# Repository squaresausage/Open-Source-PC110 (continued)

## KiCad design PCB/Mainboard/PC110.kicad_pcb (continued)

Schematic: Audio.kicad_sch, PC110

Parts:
C6, C24, C50, C270: DNP; C_0402_1005Metric; not fitted
C9, C14, C23, C152, C160, C161, C162, C204, C209, C214: 10uF; C_1206_3216Metric
C10: DNP; C_1206_3216Metric; not fitted
C11, C13, C18, C21, C22, C25: 270nF; C_0603_1608Metric
C12: 250nF; C_0603_1608Metric
C15, C85, C208: 1nF; C_0402_1005Metric
C16, C154: 100pF; C_0402_1005Metric
C19, C151, C155, C157, C203, C205, C211, C212: 150nF; C_0402_1005Metric
C20: 1.5nF; C_0402_1005Metric
C44: 5.6nF; C_0402_1005Metric
C52, C53: 22pF; C_0402_1005Metric
C54: 2.7uF; C_0805_2012Metric
C57: 100nF; C_0603_1608Metric
C62: 120nF; C_0402_1005Metric
C68, C97, C149, C213, C215: 100nF; C_0402_1005Metric
C100, C150: 10nF; C_0603_1608Metric
C147, C153, C158, C248: 1uF; C_0603_1608Metric
C148, C159, C165: DNP; C_0402_1005Metric
C164: 330nF; C_0603_1608Metric
C166, C207: 300nF; C_0603_1608Metric
D3, D5: 3D
D12, D34: DNP; 3D; not fitted
D40: N; SOT-416L
J3: Audio-Jack
J7: SPKR
L2, L5, L7, L8, L13: 1.5uH; L_0603_1608Metric
Q6: ST3; SOT-416L
R23, R30, R67, R72, R75, R88, R195, R221, R370: 0; R_0402_1005Metric
R24: 4.7k; R_0402_1005Metric
R25, R29, R34: 1k; R_0402_1005Metric
R26, R32, R69, R73: 2.2k; R_0402_1005Metric
R27, R33, R77, R147, R217, R218, R224, R243, R244, R245, R247: 470k; R_0402_1005Metric
R28: 56; R_1206_3216Metric
R35, R37, R120, R121, R219, R223: 100k; R_0402_1005Metric
R36, R71, R74, R78, R220, R227, R258: 10k; R_0402_1005Metric
R47, R48, R50, R54, R55, R56, R64, R65: DNP; R_0402_1005Metric; not fitted
R70, R364: DNP; R_0402_1005Metric
R92: 47; R_0402_1005Metric
R222, R225: 6.8k; R_0402_1005Metric
R226: 120; R_1206_3216Metric
R250: 0; R_0805_2012Metric
R256: 100; R_0805_2012Metric
U4: ES488F; QFN-52
U5: 74HC14; TSSOP-14_4.4x5mm_P0.65mm
U10: YM3812; SOP-24
U11: NJM2904M; soic-8-small
U12: LM4861; SOIC-8-narrow
U17: 3E00; SOT-23-5
U18: VT74; TSSOP-14_4.4x5mm_P0.65mm
U20: 7W14; sso-8
U31: 3F01; SOT-23-5
U34: 74LV126; TSSOP-14_4.4x5mm_P0.65mm
U46: Y3014; SOP-16
U47: 3414A; SOIC-8
U48: DS1669; SOIC-8
U49: HD151015; SSOP-24_5.3x8.2mm_P0.65mm
U64: SN74LV126; TSSOP-14_4.4x5mm_P0.65mm
U66: SN74LV02; TSSOP-14_4.4x5mm_P0.65mm
U71: SN74LV32; TSSOP-14_4.4x5mm_P0.65mm
X2: 89G6821; XTAL-1

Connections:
/Audio/Enable_YMF_Bus: R147.1, U5.5, U10.3 (IC#), U31.1 (OUT), U34.1, U34.4, U34.10, U34.13
/Audio/PCMCIA_KB_sound: C25.2 (-), R35.1
/Audio/YMFDAC_OUTPUT: C11.2 (-), R26.1
Bowman_Audio_Vol_Dn: U48.7 (DnC); also elsewhere on the board
Bowman_Audio_Vol_Up: U48.2 (UpC); also elsewhere on the board
Chipset_Sound: R74.2; also elsewhere on the board
ESS_AEN: U4.40 (AEN); also elsewhere on the board
ESS_CLK: R70.1; also elsewhere on the board
ESS_DACK1#: U4.36 (DACK1#); also elsewhere on the board
ESS_DRDY: U4.21 (DRDY), U66.6
ESS_IRQ1: R29.1, U4.16 (IRQ1); also elsewhere on the board
ESS_IRQ2: U4.18 (IRQ2); also elsewhere on the board
ESS_Sound: C18.1 (+), U4.9 (LineOut)
IOR#: R364.1, U66.3, U66.5; also elsewhere on the board
KB_Sound: R78.1; also elsewhere on the board
MIC_J17: R30.2; also elsewhere on the board
MIC_in_pin: C6.2, J3.4 (MI), L13.2 (-)
Modem_Audio_Out: R32.1; also elsewhere on the board
unnamed: C10.1 (+), C23.1 (+), L7.1 (+)
unnamed: C10.2 (-), C23.2 (-), C154.2 (-), R227.2, U47.1
unnamed: C11.1 (+), C50.2, R72.1, U11.7
unnamed: C12.1 (+), U4.1 (FoutR)
unnamed: C12.2 (-), C24.2 (-), U4.2 (CinR)
unnamed: C13.1 (+), U48.6 (RW)
unnamed: C13.2 (-), R217.2, R218.2, U47.3 (+)
unnamed: C15.2 (-), R25.2, R26.2, R32.2, R34.2, R35.2, U47.6 (-)
unnamed: C18.2 (-), R34.1
unnamed: C20.2 (-), C21.2 (-), U4.8 (CinL)
unnamed: C21.1 (+), U4.7 (FoutL)
unnamed: C22.1 (+), U4.10 (ByPass)
unnamed: C25.1 (+), Q6.3 (C), R36.2
unnamed: C85.1 (+), R24.1, R121.1, U12.4 (IN-)
unnamed: C85.2 (-), J7.2, R121.2, U12.5 (OUT+)
unnamed: C147.1 (+), U48.1 (RH)
unnamed: C15.1 (+), C147.2 (-), R25.1, U47.7
unnamed: C150.1 (+), U4.4 (MIC)
unnamed: C150.2 (-), R221.1, R225.1
unnamed: C153.1, R37.2, R217.1
unnamed: C154.1 (+), R220.1, R227.1, U47.2 (-)
unnamed: C160.2 (-), C166.1 (+), R224.1, U4.11 (ByPass)
unnamed: C162.1 (+), R222.2, R225.2
unnamed: C164.2, R220.2
unnamed: C207.1 (+), R71.2
unnamed: C213.2, C214.2, R250.1
unnamed: C270.1, U64.11
unnamed: D3.2 (K), U5.6
unnamed: D5.2 (K), Q6.2 (B), R71.1, R74.1, R78.2
unnamed: J3.3 (G), L2.2 (-)
unnamed: C148.2, J3.5 (MO), L8.2 (-)
unnamed: C165.1, J3.2 (SI), L7.2 (-)
unnamed: C159.2, J3.1 (SO), L5.1 (+)
unnamed: J7.1, U12.8 (OUT-)
unnamed: C16.1, L5.2 (-), R24.2
unnamed: L8.1 (+), R30.1
unnamed: L13.1 (+), R221.2
unnamed: R67.1, R73.2, U11.1
unnamed: R370.2, U66.10
unnamed: C152.1, C155.2, C161.1, R226.1, U4.6 (CMR)
unnamed: U4.37 (IOR), U71.11
unnamed: U4.38 (IOW), U71.8
unnamed: R23.1, U4.52 (REF)
unnamed: U4.39 (RESET), U20.5
unnamed: C213.1, U4.44 (VCC_Bus), U49.24 (VCCB)
unnamed: C52.1, R70.2, U4.34 (Xin), X2.1
unnamed: C53.2, U4.35 (Xout), X2.2
unnamed: R77.1, U10.4 (AO), U34.11
unnamed: R244.2, U10.7 (CS#), U34.3
unnamed: R64.2, U4.23 (D0), U10.10 (D0), U49.22 (B0)
unnamed: R54.2, U4.24 (D1), U10.11 (D1), U49.21 (B1)
unnamed: R47.2, U4.25 (D2), U10.13 (D2), U49.20 (B2)
unnamed: R50.2, U4.28 (D3), U10.14 (D3), U49.19 (B3)
unnamed: R65.2, U4.29 (D4), U10.15 (D4), U49.18 (B4)
unnamed: R55.1, U4.30 (D5), U10.16 (D5), U49.17 (B5)
unnamed: R48.1, U4.31 (D6), U10.17 (D6), U49.16 (B6)
unnamed: R56.1, U4.32 (D7), U10.18 (D7), U49.15 (B7)
unnamed: R92.2, U10.24 (M)
unnamed: U10.21 (MO), U46.7 (SD)
unnamed: R243.2, U10.6 (RD#), U34.6
unnamed: U10.20 (SH), U46.4 (LOAD)
unnamed: U10.23 (SY), U46.10 (Clock)
unnamed: R245.2, U10.5 (WR#), U34.8
unnamed: C214.1, R75.1, U11.3 (+)
unnamed: R67.2, U11.2 (-), U46.16 (MP)
unnamed: R72.2, U11.6 (-)
unnamed: C157.1, C209.1, R256.1, U11.8 (V+), U46.1 (VDD)
unnamed: C157.2, C209.2, R250.2, U11.4 (V-), U46.12 (GND)
unnamed: C54.1, U12.2 (Bypass), U12.3 (IN+)
unnamed: C248.2, D40.3, R247.1, U12.1 (~SD)
unnamed: U18.2 (D), U18.6 (~Q), U18.11 (C)
unnamed: R92.1, U18.8 (~Q), U18.12 (D)
unnamed: C100.1, D34.3 (A), U31.5 (CD)
unnamed: C97.1, D34.1 (A), R195.2, U31.2 (VDD)
unnamed: R75.2, U46.14 (RB)
unnamed: C158.2, R27.1, R33.1, U47.5 (+)
unnamed: R219.2, U49.11 (A8)
unnamed: R223.1, U49.14 (B8)
unnamed: R364.2, R370.1, U49.2 (DIR)
unnamed: C270.2, D3.1 (A), D3.3 (A), R258.2, U49.23 (G#)
unnamed: U66.1, U66.8
unnamed: U66.4, U66.9
PCMCIA_Sound: C207.2 (-), R120.2; also elsewhere on the board
PNET1: C208.2, C211.2, C212.1, C215.1, R120.1, R258.1, U49.1 (VCCA), U64.13; also elsewhere on the board
PNET2: C68.1, C203.2, C204.2, C205.1, D34.2 (K), R28.2, R195.1, R243.1, R244.1, R245.1, R256.2, U10.1 (VCC), U12.6 (VDD), U18.1 (~R), U18.4 (~S), U18.10 (~S), U18.13 (~R), U18.14 (VCC); also elsewhere on the board
PNET6: C9.1, C14.1, C149.2, C151.1, R27.2, R28.1, R36.1, R37.1, R222.1, U47.8 (V+), U48.8 (V+)
PWRGD_shift: C248.1; also elsewhere on the board
PWRGD_shift_buff: U71.10, U71.13; also elsewhere on the board
SA1: U4.42 (A1); also elsewhere on the board
SA2: U4.43 (A2); also elsewhere on the board
SA3: U4.45 (A3); also elsewhere on the board
SA4: U4.46 (A4); also elsewhere on the board
SA5: U4.47 (A5); also elsewhere on the board
SA6: U4.48 (A6); also elsewhere on the board
SA7: U4.49 (A7); also elsewhere on the board
SA8: U4.50 (A8); also elsewhere on the board
SA9: U4.51 (A9); also elsewhere on the board
SD0: U49.3 (A0); also elsewhere on the board
SD1: U49.4 (A1); also elsewhere on the board
SD2: U49.5 (A2); also elsewhere on the board
SD3: U49.6 (A3); also elsewhere on the board
SD4: U49.7 (A4); also elsewhere on the board
SD5: U49.8 (A5); also elsewhere on the board
SD6: U49.9 (A6); also elsewhere on the board
SD7: U49.10 (A7); also elsewhere on the board
YMF_CLK: U18.3 (C); also elsewhere on the board
YMF_CS#_Buf: U4.14 (DIR), U34.2, U64.12, U66.2
YMF_RD#_Buf: U34.5, U71.12; also elsewhere on the board
YMF_SA0_A0: U4.41 (A0), U34.12; also elsewhere on the board
YMF_WR#_Buf: U34.9, U71.9; also elsewhere on the board

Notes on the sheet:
Device_Data_BUS
Device_Address_BUS

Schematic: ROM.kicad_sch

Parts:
C246: 150nF; C_0603_1608Metric
C249, C282: 150nF; C_0402_1005Metric
D19: N; SOT-416L
D20: 3D; SOT-416L
Q35: 8C; SOT-523
Q36: 7C; TSOT-23
R112: 47k; R_0402_1005Metric
R113, R327: 470k; R_0402_1005Metric
R320: 10k; R_0402_1005Metric
R321: 100k; R_0402_1005Metric
U24: E4; SOT-353
U36: MSM538032E; SOP48
U59: 28F002BX; Flash-40
U60: E3; SOT-353

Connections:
BIOS_SA17: U59.40 (A17); also elsewhere on the board
Bowman5_Buff: U60.1; also elsewhere on the board
Chipset_BIOS_CE#: U59.22 (CE#); also elsewhere on the board
Chipset_SA16: U59.1 (A16); also elsewhere on the board
D28_1: Q36.2 (E); also elsewhere on the board
MEMR#: U36.16 (OE#), U59.24 (OE#); also elsewhere on the board
MEMW#: U24.1; also elsewhere on the board
unnamed: C246.1 (+), D20.1, Q36.3 (C), R327.1, U59.11 (VPP)
unnamed: D19.1, D19.2, R112.2, U24.2
unnamed: Q35.1 (B), R321.2
unnamed: Q35.3 (C), R320.1
unnamed: Q36.1 (B), R320.2
unnamed: R321.1, U60.4
unnamed: D20.3, R113.2, U59.10 (RP#)
unnamed: U24.4, U59.9 (WE#)
OKI_CE#: U36.14 (CE#); also elsewhere on the board
OKI_SA12: U36.40 (A12); also elsewhere on the board
OKI_SA13: U36.39 (A13); also elsewhere on the board
OKI_SA14: U36.38 (A14); also elsewhere on the board
OKI_SA15: U36.37 (A15); also elsewhere on the board
OKI_SA16: U36.36 (A16); also elsewhere on the board
OKI_SA17: U36.5 (A17); also elsewhere on the board
OKI_SA18: U36.4 (A18); also elsewhere on the board
OKI_SA19: U36.45 (A19); also elsewhere on the board
PNET7: C249.2 (-), C282.1 (+), R112.1, U24.5 (VCC), U36.25 (VCC), U36.35 (BHE), U59.30 (VCC), U59.31 (VCC); also elsewhere on the board
PWRGD: D20.2; also elsewhere on the board
PWRGD_shift_buff: U60.2; also elsewhere on the board
Pluto_BIOS_WR_EN: D19.3; also elsewhere on the board
SA0: U59.21 (A0); also elsewhere on the board
SA1: U36.13 (A0), U59.20 (A1); also elsewhere on the board
SA2: U36.12 (A1), U59.19 (A2); also elsewhere on the board
SA3: U36.11 (A2), U59.18 (A3); also elsewhere on the board
SA4: U36.10 (A3), U59.17 (A4); also elsewhere on the board
SA5: U36.9 (A4), U59.16 (A5); also elsewhere on the board
SA6: U36.8 (A5), U59.15 (A6); also elsewhere on the board
SA7: U36.7 (A6), U59.14 (A7); also elsewhere on the board
SA8: U36.6 (A7), U59.8 (A8); also elsewhere on the board
SA9: U36.44 (A8), U59.7 (A9); also elsewhere on the board
SA10: U36.43 (A9), U59.36 (A10); also elsewhere on the board
SA11: U36.42 (A10), U59.6 (A11); also elsewhere on the board
SA12: U36.41 (A11), U59.5 (A12); also elsewhere on the board
SA13: U59.4 (A13); also elsewhere on the board
SA14: U59.3 (A14); also elsewhere on the board
SA15: U59.2 (A15); also elsewhere on the board
SD0: U36.17 (D0), U59.25 (DQ0); also elsewhere on the board
SD1: U36.19 (D1), U59.26 (DQ1); also elsewhere on the board
SD2: U36.21 (D2), U59.27 (DQ2); also elsewhere on the board
SD3: U36.23 (D3), U59.28 (DQ3); also elsewhere on the board
SD4: U36.26 (D4), U59.32 (DQ4); also elsewhere on the board
SD5: U36.28 (D5), U59.33 (DQ5); also elsewhere on the board
SD6: U36.30 (D6), U59.34 (DQ6); also elsewhere on the board
SD7: U36.32 (D7), U59.35 (DQ7); also elsewhere on the board
SD8: U36.18 (D8); also elsewhere on the board
SD9: U36.20 (D9); also elsewhere on the board
SD10: U36.22 (D10); also elsewhere on the board
SD11: U36.24 (D11); also elsewhere on the board
SD12: U36.27 (D12); also elsewhere on the board
SD13: U36.29 (D13); also elsewhere on the board
SD14: U36.31 (D14); also elsewhere on the board
SD15: U36.33 (D15); also elsewhere on the board

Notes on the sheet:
Device_Data_BUS
Device_Address_BUS
OKI_Extra_Address

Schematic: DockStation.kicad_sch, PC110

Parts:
C1: DNP; C_0402_1005Metric; not fitted
C2, C235, C237, C239, C265: 150nF; C_0402_1005Metric
C3, C7, C91, C93: 100nF; C_0402_1005Metric
C4: 1nF; C_0402_1005Metric
C86, C88: 180nF; C_0402_1005Metric
C89: 470nF; C_0603_1608Metric
C90, C92, C198, C243: 120nF; C_0402_1005Metric
C163, C167, C170, C199: 220pF; C_0402_1005Metric
C168, C238: 1uF; C_0603_1608Metric
C197, C240: 300nF; C_0603_1608Metric
C200, C201: 10uF; C_1206_3216Metric
C202: 150nF; C_0603_1608Metric
D1: 3D
D39, D55: s.3 5F; Diode
D52, D53, D54, D56, D57: K; SOT-416
D59: 3D; SOT-416L
EM5: R-array
F2: 1.0A; Fuse_1206_3216Metric
F3: 0.5A; Fuse_1206_3216Metric
J1: PS2
J8: Modem-Connector
J13: Docking Port
L1: 1.5uH; L_0603_1608Metric
L12: 300nH; L_0805_2012Metric
Q24: 6D; SOT-23
Q25, Q33, Q34: BH RT; SOT-89-3
Q32: 8B; SOT-416
R4: 4.7k; R_0402_1005Metric
R8: 300; R_0402_1005Metric
R122, R123, R124, R125, R127, R130, R135, R139, R144, R183, R187, R189, R190, R191, R194, R228, R302, R303, R305, R306, R307, R309, R311: 470k; R_0402_1005Metric
R181, R188, R192, R193, R289: 10k; R_0402_1005Metric
R230: 0; R_0805_2012Metric
R231: 0; R_0603_1608Metric
R238: 56; R_0603_1608Metric
R241: 8.2; R_1206_3216Metric_Pad1.30x1.75mm_HandSolder
R242: 7.5k; R_0402_1005Metric
R291, R297: 220; R_0402_1005Metric
R293: 22k; R_0402_1005Metric
R294: 1.2k; R_0402_1005Metric
RA2: 10k; R-array
U1: EA; SOT-353
U2: 7W32; sso-8
U3: HSDL-1000 X03; IRDA
U20: 7W14; sso-8
U26: 7W126; sso-8
U57: SN74LVT125; TSSOP-14_4.4x5mm_P0.65mm
U64: SN74LV126; TSSOP-14_4.4x5mm_P0.65mm
U71: SN74LV32; TSSOP-14_4.4x5mm_P0.65mm

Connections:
Dock_PWR_IN-: J13.53 (J13_53), J13.54 (J13_53), J13.55 (J13_53), J13.56 (J13_53), J13.57 (J13_53); also elsewhere on the board
EN_RS232: J13.79 (EN_RS232); also elsewhere on the board
Enable_IRDA_Buf: Q24.1 (B), R242.2, U26.1 (C), U26.7 (~PRE), U57.4, U57.10; also elsewhere on the board
FDC_ACK#: J13.71 (ACK#); also elsewhere on the board
FDC_AUTOFD#: J13.73 (AUTOFD#); also elsewhere on the board
FDC_BUSY: J13.22 (BUSY); also elsewhere on the board
FDC_CTS1#: J8.8 (CTS1#), R191.1; also elsewhere on the board
FDC_CTS2#: J13.82 (CTS2#), R303.2; also elsewhere on the board
FDC_DCD1#: J8.4 (DCD1#), R187.1; also elsewhere on the board
FDC_DCD2#: J13.17 (DCD2#), R309.2; also elsewhere on the board
FDC_DIR#: J13.7 (FDC_DIR#); also elsewhere on the board
FDC_DRATE0: R302.2, U57.2; also elsewhere on the board
FDC_DRATE1: R306.2, U57.12; also elsewhere on the board
FDC_DSKCHG#: J13.12 (FDC_DSKCHG#), R122.2; also elsewhere on the board
FDC_DSR1: J8.7 (DSR1), R189.1; also elsewhere on the board
FDC_DSR2#: J13.84 (DSR2#), R305.2; also elsewhere on the board
FDC_DTR1#: R192.1, U64.9; also elsewhere on the board
FDC_DTR2#: J13.20 (DTR2#); also elsewhere on the board
FDC_ERROR#: J13.77 (ERROR#); also elsewhere on the board
FDC_HDSEL#: J13.11 (FDC_HDSEL#); also elsewhere on the board
FDC_INIT#: J13.72 (INIT#); also elsewhere on the board
FDC_IRRX_RXD2: U26.3 (~Q), U57.8; also elsewhere on the board
FDC_IRTX_TXD2: R183.2, U26.2 (D), U57.5; also elsewhere on the board
FDC_PD0: J13.30 (PD0); also elsewhere on the board
FDC_PD1: J13.29 (PD1); also elsewhere on the board
FDC_PD2: J13.28 (PD2); also elsewhere on the board
FDC_PD3: J13.27 (PD3); also elsewhere on the board
FDC_PD4: J13.26 (PD4); also elsewhere on the board
FDC_PD5: J13.25 (PD5); also elsewhere on the board
FDC_PD6: J13.76 (PD6); also elsewhere on the board
FDC_PD7: J13.24 (PD7); also elsewhere on the board
FDC_PE: J13.78 (PE); also elsewhere on the board
FDC_RDATA#: J13.91 (FDC_RDATA#), R307.2; also elsewhere on the board
FDC_RI1#: J8.5 (RI1#), R190.1; also elsewhere on the board
FDC_RI2#: J13.81 (RI2#), R311.1; also elsewhere on the board
FDC_RTS1#: R193.1, U64.5; also elsewhere on the board
FDC_RTS2#: J13.83 (RTS2#); also elsewhere on the board
FDC_RXD1: J8.10 (RXD1), R194.1; also elsewhere on the board
FDC_SLCT: J13.23 (SLCT); also elsewhere on the board
FDC_SLCTIN#: J13.74 (SLCTIN#); also elsewhere on the board
FDC_STEP#: J13.94 (FDC_STEP#); also elsewhere on the board
FDC_STROBE#: J13.31 (STROBE#); also elsewhere on the board
FDC_TRK0#: J13.9 (FDC_TRK0), R124.2; also elsewhere on the board
FDC_TXD1: R188.1, U64.2; also elsewhere on the board
FDC_TXD2_EN: R8.1, U2.5, U57.6
FDC_UART1_EN: U64.1, U64.4, U64.10; also elsewhere on the board
FDC_WDATA#: J13.8 (FDC_WDATA#); also elsewhere on the board
FDC_WGATE#: J13.93 (FDC_WGATE#); also elsewhere on the board
FDC_WRTPRT#: J13.10 (FDC_WRTPRT#), R125.1; also elsewhere on the board
FDD_Bowman: J13.90 (FDD_Bowman), R144.2; also elsewhere on the board
FDD_DRSEL: J13.5 (FDD_DRSEL); also elsewhere on the board
FDD_INDEX#: J13.4 (FDD_INDEX#), R123.2; also elsewhere on the board
FDD_MOTEN: J13.6 (FDD_MOTEN); also elsewhere on the board
FDD_Pluto1: J13.98 (FDD_Pluto1); also elsewhere on the board
FDD_Pluto2: J13.97 (FDD_Pluto2); also elsewhere on the board
FDD_Pluto3: J13.95 (FDD_Pluto3); also elsewhere on the board
FDD_Pluto4: J13.92 (FDD_Pluto4); also elsewhere on the board
KB_INIT1: EM5.5, J13.14 (KB_INT1), RA2.5 (R4.2); also elsewhere on the board
KB_INIT2: EM5.6, J13.15 (KB_INT2), RA2.6 (R3.2); also elsewhere on the board
KB_INIT3: EM5.8, J13.86 (KB_INT3), RA2.8 (R1.2); also elsewhere on the board
KB_INIT4: EM5.7, J13.87 (KB_INT4), RA2.7 (R2.2); also elsewhere on the board
KB_SPKUP_DN: D59.3 (A), J13.63 (KB_SPKUP_DN); also elsewhere on the board
KB_SRDY#_shift: R294.1; also elsewhere on the board
M38_P16_R86: J13.62 (M38_P16); also elsewhere on the board
M38_P34: J13.38 (M38_P34); also elsewhere on the board
M38_P46: J13.39 (M38_P46); also elsewhere on the board
M38_P67: J13.61 (M38_P67); also elsewhere on the board
MN192_VSEN#: J8.16 (VSEN#); also elsewhere on the board
MN195_U1RD#: J8.3 (U1RD#); also elsewhere on the board
Modem_Audio_Out: C89.1 (+); also elsewhere on the board
Modem_VSDA#: J8.17 (VSDA#), R127.1; also elsewhere on the board
unnamed: C1.2 (-), U2.1, U3.1 (IRDA_RXA)
unnamed: C4.1 (+), D1.1 (A), D1.3 (A), R4.1, U1.2
unnamed: C7.1 (+), J1.7 (PS2_Pluto), L1.2
unnamed: C89.2 (-), J8.18 (VPCK#)
unnamed: C92.2 (-), F3.1, J13.16 (PS/2_Power), L12.1, RA2.1 (R1.1), RA2.2 (R2.1), RA2.3 (R3.1), RA2.4 (R4.1)
unnamed: C163.2 (-), EM5.3, J1.6 (KB_INIT2)
unnamed: C167.2 (-), EM5.4, J1.2 (KB_INIT1)
unnamed: C168.2 (-), U3.3 (PIN_Bypass)
unnamed: C170.1 (+), EM5.1, J1.5 (KB_INIT3)
unnamed: C197.2 (-), U3.5 (Daylight_Cancellation)
unnamed: C198.1 (+), J1.4 (5V), L12.2
unnamed: C199.1 (+), EM5.2, J1.3 (KB_INIT4)
unnamed: C200.2 (-), R241.1, U3.8 (IRDA_LED_A)
unnamed: C201.1 (+), C202.2 (-), R238.1, U3.6 (IRDA_Supply)
unnamed: C238.1 (+), Q33.1 (B), R293.1, R297.2
unnamed: C93.1 (+), C238.2 (-), C239.2 (-), J13.13 (FDD_PWR), J13.88 (FDD_PWR), J13.89 (FDD_PWR), Q33.2 (C)
unnamed: C240.1 (+), Q34.1 (B), R294.2
unnamed: C240.2 (-), F3.2, Q34.2 (C)
unnamed: D1.2 (K), R4.2, U2.3
unnamed: D39.2 (A), D55.2 (A), J13.46 (PNET4), J13.48 (PNET4)
unnamed: J1.1 (GND), R231.2
unnamed: J1.8 (GND), R230.2
unnamed: J8.6 (DRT1#), U64.8
unnamed: J8.9 (RTS1#), U64.6
unnamed: J8.11 (TXD1), U64.3
unnamed: J13.96 (FDD_DRATE0), U57.3
unnamed: J13.3 (FDD_DRATE1), U57.11
unnamed: J8.21 (ADCK#), J13.59 (Modem_ADCK#)
unnamed: J8.20 (IRQ1#), J13.60 (Modem_IRQ1#)
unnamed: J8.24 (RSRVD2), J13.42 (Modem_RSRVD1)
unnamed: J8.23 (RSRVD1), J13.41 (Modem_RSRVD2)
unnamed: J8.22 (S11), J13.58 (Modem_S11)
unnamed: J8.19 (VPDA#), J13.52 (Modem_VPDA#)
unnamed: J13.18 (RXD2), R135.1, U26.5 (Q)
unnamed: J13.19 (TXD2), U26.6 (~CLR)
unnamed: Q24.3 (C), R238.2
unnamed: Q25.1 (B), R242.1
unnamed: Q25.2 (C), R241.2
unnamed: Q32.1 (B), R289.2
unnamed: Q32.3 (C), R291.1
unnamed: F2.1, Q33.3 (E), R293.2
unnamed: R289.1, U20.2
unnamed: R291.2, R297.1
unnamed: U1.4, U2.2
unnamed: U2.7, U57.9
unnamed: R8.2, U3.7 (IRDA_TXD)
unnamed: U20.6, U57.1, U57.13, U71.3
PNET1: D52.2 (K), D53.2 (K), D54.2 (K), D56.2 (K), D57.2 (K), R127.2, R228.1, U64.14 (VCC); also elsewhere on the board
PNET2: C2.1 (+), C3.1 (+), C235.1 (+), C237.1 (+), J13.21 (PNET2), J13.80 (PNET2), R183.1, U1.5 (VCC), U2.8 (VCC); also elsewhere on the board
PNET4: D39.1 (K), D55.1 (K); also elsewhere on the board
PNET7: R130.1, R139.1, R144.1; also elsewhere on the board
PS2_L1_Pluto: L1.1, R228.2; also elsewhere on the board
PWRGD_shift_buff: R181.2, U71.1; also elsewhere on the board
Pluto_Dock_IO1: J13.2 (Pluto_Dock1), R139.2; also elsewhere on the board
Pluto_Dock_IO2: J13.99 (Pluto_Dock2), R130.2; also elsewhere on the board
Pluto_IRDA_OUT: U2.6; also elsewhere on the board
Pluto_Switched_PNET5: C86.1 (+), J8.12 (PNET5_Pluto), J8.15 (PNET5_Pluto), R187.2, R189.2, R190.2, R191.2, R194.2; also elsewhere on the board
U71_OR1_IN2: U71.2; also elsewhere on the board
VCC: C88.2 (-), J8.2 (VCC), J8.25 (VCC); also elsewhere on the board
VGA_Blue: D54.3 (COM), J13.65 (VGA_Blue); also elsewhere on the board
VGA_Green: D53.3 (COM), J13.67 (VGA_Green); also elsewhere on the board
VGA_HSync: D56.3 (COM), J13.36 (VGA_HSync); also elsewhere on the board
VGA_Red: D52.3 (COM), J13.69 (VGA_Red); also elsewhere on the board
VGA_VSync: D57.3 (COM), J13.33 (VGA_VSync); also elsewhere on the board
YellowWire1_2: R181.1; also elsewhere on the board

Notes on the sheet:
Enables all external PS/2 devices; PS/2 conn on PC110 and dock

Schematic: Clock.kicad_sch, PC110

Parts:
C56: 100nF; C_0402_1005Metric
C59: 10nF; C_0603_1608Metric
C227, C256: 150nF; C_0402_1005Metric; Rating V
C230, C257, C261: DNP; C_0402_1005Metric; Rating V
C232: 10uF; C_1206_3216Metric; Rating V
C242: 100nF; C_0402_1005Metric; Rating V
C254, C260: 1nF; C_0402_1005Metric; Rating V
C258: 220pF; C_0402_1005Metric; Rating V
C259: 330nF; C_0603_1608Metric; Rating V
D9: DNP; 3D
Q31: MUN2114; SOT-23
R79: 0; R_0402_1005Metric
R91: 470k; R_0402_1005Metric
R275: 4.7k; R_0402_1005Metric
R284: 10; R_0805_2012Metric
R332, R340, R341, R348, R350, R359: 33; R_0402_1005Metric
R344: DNP; R_0402_1005Metric
R353: 56; R_0402_1005Metric
R357, R358: 47; R_0402_1005Metric
U16: BD53E31; SOT-23-5
U62: 74LS125; TSSOP-14_4.4x5mm_P0.65mm
U63: AV9154A-27; SOIC-16W
U66: 74LS02; TSSOP-14_4.4x5mm_P0.65mm
X4: 59G3482; XTAL-6

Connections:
Bowman_CLK: R340.2; also elsewhere on the board
Chipset_2XCPU_CLK: R359.2; also elsewhere on the board
Chipset_CLK: R341.1; also elsewhere on the board
ESS_CLK: R344.2; also elsewhere on the board
FDC_CLK: R332.2; also elsewhere on the board
unnamed: C227.2 (-), D9.2 (K), Q31.3 (C), R79.1, R275.1, R284.1, U63.10 (FS2), U63.16 (FS0)
unnamed: C230.2 (-), C257.2 (-), U63.2 (X2), X4.2
unnamed: C232.2 (-), C258.2 (-), C259.2 (-), C260.2 (-), R284.2, U63.4 (VCC), U63.13 (VCC)
unnamed: C257.1 (+), C261.1 (+), U63.3 (X1), X4.1
unnamed: Q31.1 (B), U66.13
unnamed: R332.1, R340.1, U62.8
unnamed: R341.2, R348.2, U62.6
unnamed: R344.1, R353.1, U62.11
unnamed: R350.2, U62.3
unnamed: R357.1, U62.2, U62.5, U62.12
unnamed: R358.1, U62.9
unnamed: C59.1, D9.3 (A), U16.5 (CD)
unnamed: R91.1, U16.1 (OUT), U63.9 (OE)
unnamed: C56.1, D9.1 (A), R79.2, U16.2 (VDD)
unnamed: R359.1, U63.14 (3XCPUCLK)
unnamed: R357.2, U63.11 (14.318MHz)
unnamed: R358.2, U63.6 (24MHz)
PNET1: C242.2 (-), C254.2 (-), C256.2 (-), Q31.2 (E), U62.14 (VCC), U66.14 (VCC); also elsewhere on the board
PWRGD: U66.12; also elsewhere on the board
Pluto_CLK: R348.1; also elsewhere on the board
RESET: U66.11; also elsewhere on the board
VGA_CLK: R350.1; also elsewhere on the board
YMF_CLK: R353.2; also elsewhere on the board

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
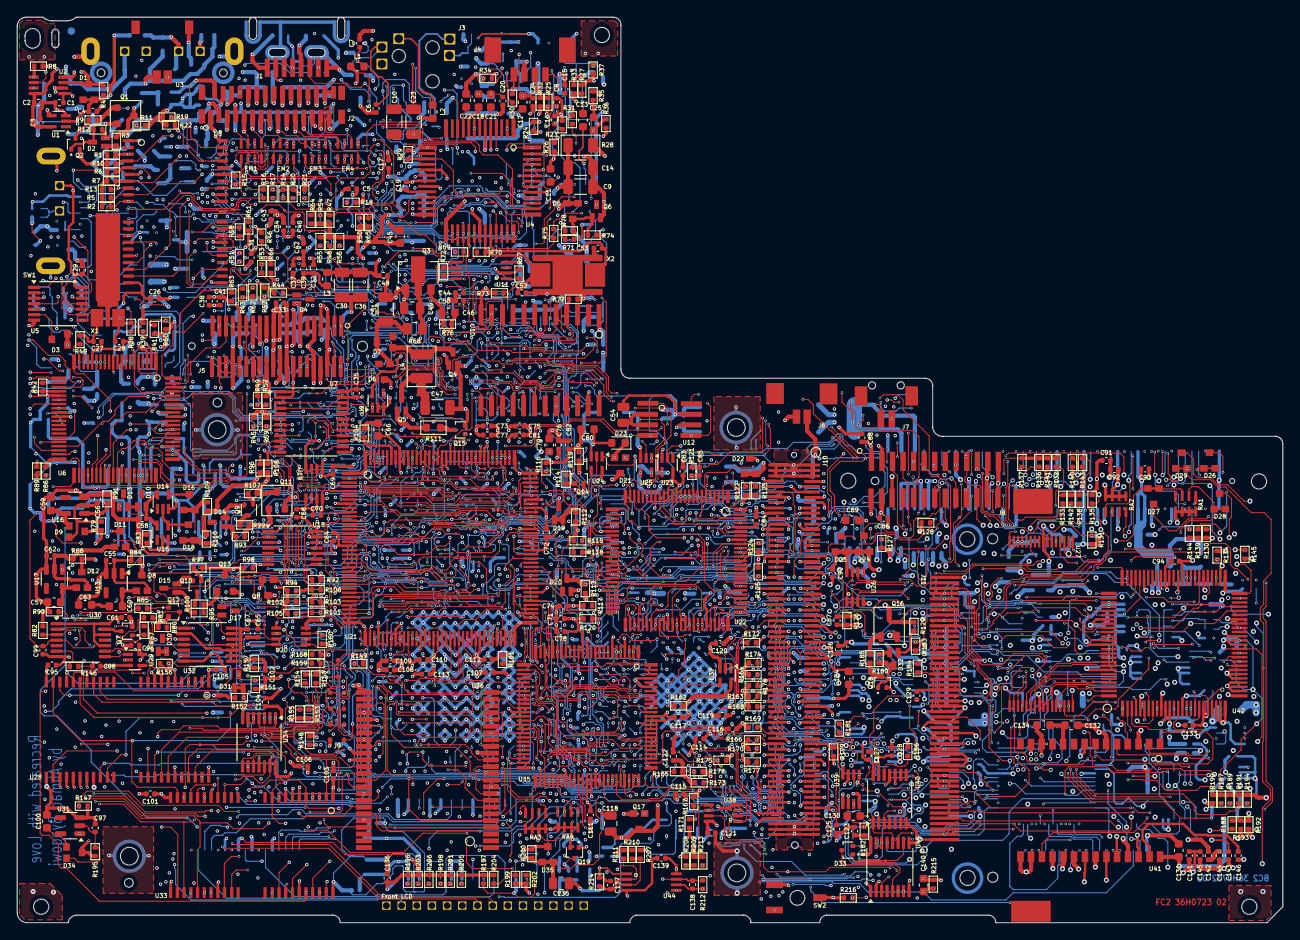
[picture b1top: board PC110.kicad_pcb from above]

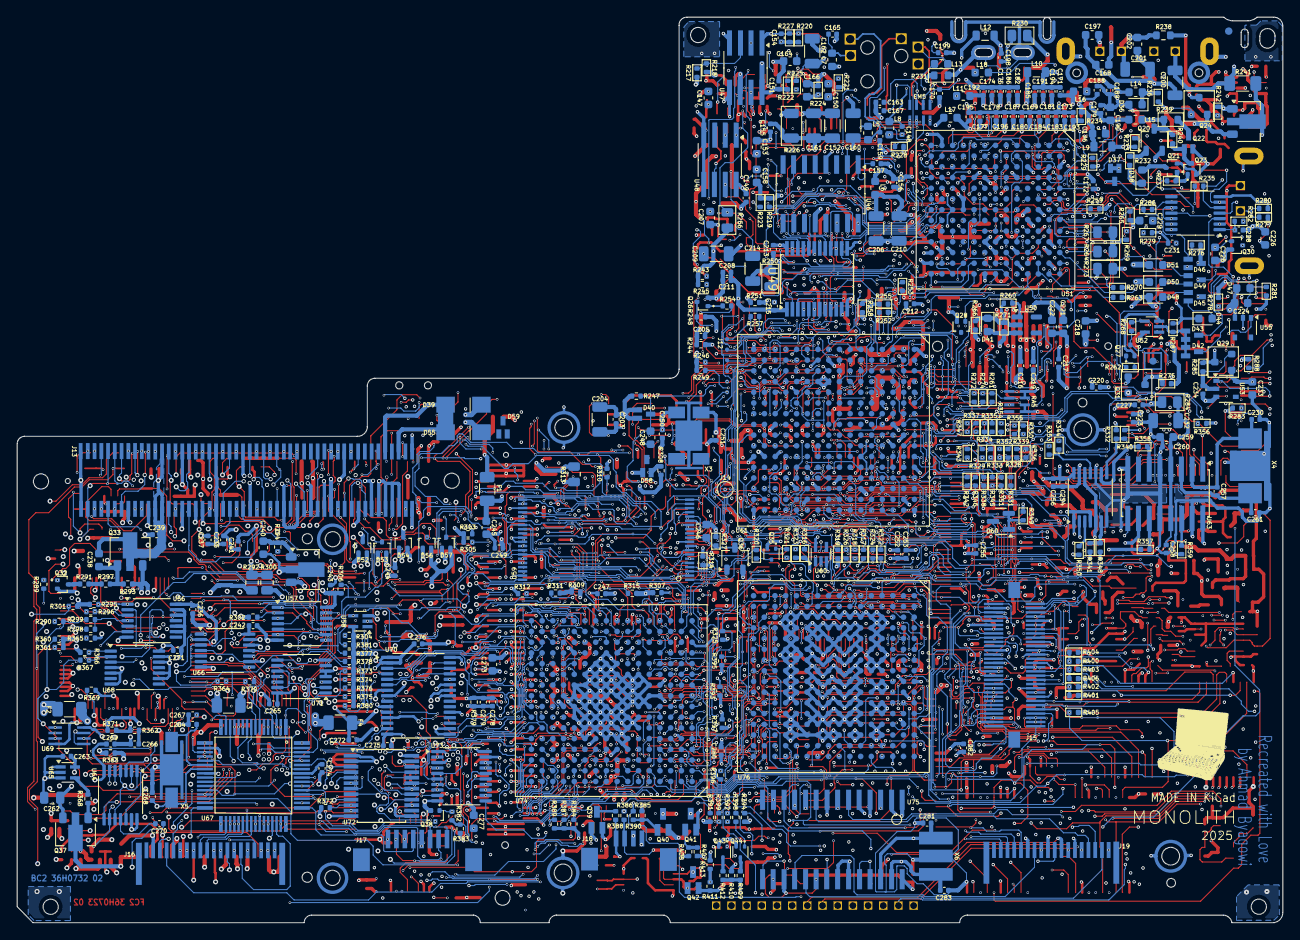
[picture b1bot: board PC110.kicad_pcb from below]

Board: 10 copper layers, 150.1 x 107.4 mm, 936 parts (448 on the bottom side), 1141 nets.

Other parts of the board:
G1: LOGO; logo

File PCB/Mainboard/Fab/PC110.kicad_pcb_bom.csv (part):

Designator,Quantity,Value,Footprint,Package,MPN,DNP,Mount_Type,Description
C1,1,DNP,C_0402_1005Metric,,,Yes,smt,
C10,1,DNP,C_1206_3216Metric,,,Yes,smt,
"C100, C131, C150, C190, C222, C224, C245, C46, C59",9,10nF,C_0603_1608Metric,,,,smt,
"C101, C109, C61, C74, C86, C88",6,180nF,C_0402_1005Metric,,,,smt,
"C102, C113, C198, C243, C244, C255, C279, C29, C41, C62, C73, C87, C90, C92",14,120nF,C_0402_1005Metric,,,,smt,
"C103, C104, C105, C108, C112, C123, C126, C128, C136, C142, C143, C151, C155, C157, C17, C19, C2, C203, C205, C211, C212, C216, C217, C219, C220, C223, C227, C231, C234, C235, C237, C239, C249, C253, C256, C26, C265, C271, C272, C278, C282, C31, C32, C33, C35, C39, C42, C5, C65, C8, C95, C96",52,150nF,C_0402_1005Metric,,,,smt,
"C106, C107, C110, C111, C125, C137, C138, C15, C179, C188, C208, C247, C252, C254, C260, C34, C37, C38, C4, C40, C43, C64, C69, C71, C77, C78, C81, C85",28,1nF,C_0402_1005Metric,,,,smt,
"C11, C13, C18, C21, C22, C25, C45",7,270nF,C_0603_1608Metric,,,,smt,
"C114, C115, C116, C117, C119, C120, C121, C122, C127, C129, C133, C139, C141, C146, C149, C156, C172, C189, C213, C215, C236, C241, C242, C263, C274, C275, C276, C280, C3, C55, C56, C58, C67, C68, C7, C70, C72, C75, C76, C82, C83, C84, C91, C93, C94, C97",46,100nF,C_0402_1005Metric,,,,smt,
"C118, C135, C54",3,2.7uF,C_0805_2012Metric,,,,smt,
C12,1,250nF,C_0603_1608Metric,,,,smt,
"C124, C134, C202, C218, C221, C246, C273",7,150nF,C_0603_1608Metric,,,,smt,
"C130, C140, C147, C153, C158, C168, C225, C226, C229, C238, C248, C277, C66, C79",14,1uF,C_0603_1608Metric,,,,smt,
"C132, C57, C60, C63",4,100nF,C_0603_1608Metric,,,,smt,
"C14, C152, C160, C161, C162, C200, C201, C204, C206, C209, C210, C214, C23, C232, C30, C36, C51, C9",18,10uF,C_1206_3216Metric,,,,smt,
"C144, C145, C154, C16, C228, C99",6,100pF,C_0402_1005Metric,,,,smt,
C148,1,DNP,C_0402_1005Metric,,,Yes,smt,
C159,1,DNP,C_0402_1005Metric,,,Yes,smt,
"C163, C167, C170, C199, C258, C269",6,220pF,C_0402_1005Metric,,,,smt,
"C164, C233, C259",3,330nF,C_0603_1608Metric,,,,smt,
C165,1,DNP,C_0402_1005Metric,,,Yes,smt,
"C166, C197, C207, C240",4,300nF,C_0603_1608Metric,,,,smt,
"C169, C171, C173, C174, C175, C177, C178, C180, C181, C182, C183, C184, C185, C186, C187, C191, C192, C193, C194, C195, C196, C264",22,56pF,C_0402_1005Metric,,,,smt,
"C176, C89",2,470nF,C_0603_1608Metric,,,,smt,
C20,1,1.5nF,C_0402_1005Metric,,,,smt,
C230,1,DNP,C_0402_1005Metric,,,Yes,smt,
C24,1,DNP,C_0402_1005Metric,,,Yes,smt,
"C250, C251, C27, C28",4,18pF,C_0402_1005Metric,,,,smt,
C257,1,DNP,C_0402_1005Metric,,,Yes,smt,
C261,1,DNP,C_0402_1005Metric,,,Yes,smt,
C262,1,1.5uF,C_0805_2012Metric,,,,smt,
C266,1,180pF,C_0402_1005Metric,,,,smt,
C267,1,DNP,C_0402_1005Metric,,,Yes,smt,
C268,1,56pf,C_0402_1005Metric,,,,smt,
C270,1,DNP,C_0402_1005Metric,,,Yes,smt,
"C281, C283",2,39pF,C_0402_1005Metric,,,,smt,
C44,1,5.6nF,C_0402_1005Metric,,,,smt,
C47,1,5.6uF,C_1206_3216Metric,,,,smt,
C48,1,330nF,C_0402_1005Metric,,,,smt,
C49,1,2.2uF,C_0805_2012Metric,,,,smt,
C50,1,DNP,C_0402_1005Metric,,,Yes,smt,
"C52, C53",2,22pF,C_0402_1005Metric,,,,smt,
C6,1,DNP,C_0402_1005Metric,,,Yes,smt,
C80,1,1uF,C_0603_1608Metric,,,Yes,smt,
C98,1,330pF,C_0402_1005Metric,,,,smt,
"D1, D16, D18, D21, D22, D24, D25, D26, D27, D28, D29, D3, D35, D5",14,3D,3D,,,,smt,
"D10, D13, D2, D32, D58",5,K,SOT-416L,,,,smt,
D11,1,DNP,3D,,,Yes,smt,
D12,1,DNP,3D,,,Yes,smt,
"D14, D15, D17, D19, D30, D31, D37, D4, D40, D42, D43, D45, D46, D49",14,N,SOT-416L,,,,smt,
"D20, D59",2,3D,SOT-416L,,,,smt,
D23,1,92,D_0603_1608Metric,,,,smt,
D33,1,N,SOT-416,,,,smt,
D34,1,DNP,3D,,,Yes,smt,
D36,1,71,D_0603_1608Metric,,,,smt,
D38,1,40,D_0603_1608Metric,,,,smt,
"D39, D55",2,s.3 5F,Diode,,,,smt,
"D41, D47",2,24,D_0603_1608Metric,,,,smt,
D44,1,83,D_0603_1608Metric,,,,smt,
D48,1,A2,D_0603_1608Metric,,,,smt,
D50,1,26,D_0603_1608Metric,,,,smt,
D51,1,C6,D_0603_1608Metric,,,,smt,
"D52, D53, D54, D56, D57",5,K,SOT-416,,,,smt,
"D6, D7",2,Q,3D,,,,smt,
D60,1,3D,SOT-23,,,,smt,
D8,1,DNP,3D,,,Yes,smt,
D9,1,DNP,3D,,,Yes,smt,
"EM1, EM2, EM3, EM4, EM5",5,R-array,R-array,,,,smt,
"F1, F3, F4",3,0.5A,Fuse_1206_3216Metric,,,,smt,
F2,1,1.0A,Fuse_1206_3216Metric,,,,smt,
J1,1,PS2,PS2,,,,smt,
J10,1,PCMCIA,PCMCIA,,,,smt,
J11,1,CF-card,CF-card,,,,smt,
J12,1,Debug-6,Debug-6,,,,smt,
J13,1,Docking Port,Docking Port,,,,smt,
J15,1,RAM Module,RAM Module,,,,smt,
J16,1,Flat-20,Flat-20,,,,smt,
J17,1,Flat-8,Flat-8,,,,smt,
J18,1,Flat-4,Flat-4,,,,smt,
J19,1,Flat-18,Flat-18,,,,smt,
J2,1,LCD_connector,LCD_connector,,,,smt,
J3,1,Audio-Jack,Audio-Jack,,,,smt,
J4,1,connector-4,connector-4,,,,smt,
J5,1,PSU_Connector,PSU_Connector,,,,smt,
J6,1,BridgeBatt,BridgeBatt,,,,smt,
J7,1,SPKR,SPKR,,,,smt,
J8,1,Modem-Connector,Modem-Connector,,,,smt,
J9,1,Debug-10,Debug-10,,,,smt,
"L1, L11, L13, L14, L15, L16, L17, L18, L2, L3, L5, L6, L7, L8",14,1.5uH,L_0603_1608Metric,,,,smt,
"L10, L12, L9",3,300nH,L_0805_2012Metric,,,,smt,
L4,1,68uH,L_1210_3225Metric,,,,smt,
"Q1, Q11, Q13",3,IS6,SOT-23,,,,smt,
"Q10, Q12, Q14, Q18, Q2, Q26, Q27, Q30, Q38, Q7",10,8C,SOT-416,,,,smt,
"Q15, Q19, Q21, Q23, Q32",5,8B,SOT-416,,,,smt,
Q16,1,IS6,TSOT-23,,,,smt,
"Q17, Q8",2,6D,3D,,,,smt,
"Q20, Q36",2,7C,TSOT-23,,,,smt,
"Q22, Q4",2,YQ,SOT-416L,,,,smt,
"Q24, Q31",2,6D,SOT-23,,,,smt,
"Q25, Q33, Q34, Q37",4,BH RT,SOT-89-3,,,,smt,
Q28,1,8LR,SOT-416,,,,smt,
Q29,1,DNP,SOT-23,,,Yes,smt,
Q3,1,582 B74,SOT-89-3,,,,smt,
"Q35, Q9",2,8C,SOT-523,,,,smt,
"Q39, Q40",2,HQ,TSOT-23,,,,smt,
"Q41, Q42",2,CQ,TSOT-23,,,,smt,
"Q43, Q44",2,8B,SOT-523,,,,smt,
Q5,1,HQ,SOT-416L,,,,smt,
Q6,1,ST3,SOT-416L,,,,smt,
"R1, R10, R102, R105, R11, R113, R119, R122, R123, R124, R125, R126, R127, R128, R13, R130, R135, R139, R144, R146, R147, R148, R15, R152, R156, R158, R160, R161, R162, R173, R18, R182, R183, R186, R187, R189, R19, R190, R191, R194, R2, R215, R216, R217, R218, R22, R224, R228, R229, R233, R235, R243, R244, R245, R247, R248, R259, R262, R269, R27, R278, R282, R287, R302, R303, R305, R306, R307, R309, R311, R314, R315, R327, R33, R360, R361, R379, R5, R6, R61, R7, R77, R80, R82, R83, R90, R91, R94",88,470k,R_0402_1005Metric,,,,smt,
"R100, R291, R297",3,220,R_0402_1005Metric,,,,smt,
"R101, R103, R106, R149, R154, R159, R251, R252, R255, R257, R261, R272, R274, R317, R318, R322, R324, R326, R329, R332, R333, R334, R335, R337, R338, R340, R341, R342, R343, R345, R346, R347, R348, R350, R352, R357, R359, R46, R53",39,33,R_0402_1005Metric,,,,smt,
"R104, R112, R114, R117, R165, R171, R177, R196, R197, R200, R204, R206, R240, R246, R249, R254, R280, R288, R312, R356, R385, R39, R393, R397, R40, R408, R411, R85, R93, R95, R96",31,47k,R_0402_1005Metric,,,,smt,
"R107, R276, R383",3,33k,R_0402_1005Metric,,,,smt,
"R108, R185, R24, R263, R265, R270, R275, R279, R283, R304, R328, R330, R331, R336, R339, R351, R354, R355, R373, R374, R375, R376, R377, R378, R38, R380, R381, R4, R42, R86, R89, R9, R98",33,4.7k,R_0402_1005Metric,,,,smt,
"R109, R110, R115, R134, R143, R163, R164, R166, R168, R169, R170, R172, R174, R175, R176, R178, R179, R181, R188, R192, R193, R198, R203, R220, R227, R232, R237, R258, R281, R289, R320, R325, R36, R365, R384, R389, R391, R395, R396, R41, R71, R74, R78, R97",44,10k,R_0402_1005Metric,,,,smt,
R111,1,100,R_0603_1608Metric,,,,smt,
"R116, R118, R120, R121, R150, R151, R153, R155, R157, R167, R201, R205, R209, R212, R214, R219, R223, R234, R268, R310, R321, R349, R35, R363, R37, R372, R390, R401, R404, R405, R406, R407, R413, R44, R45, R49, R57, R59, R81, R87",40,100k,R_0402_1005Metric,,,,smt,
R12,1,182k,R_0402_1005Metric,,,,smt,
"R129, R260",2,133k,R_0402_1005Metric,,,,smt,
R131,1,DNP,R_0402_1005Metric,,,Yes,smt,
"R132, R133, R137, R362, R371",5,2k,R_0402_1005Metric,,,,smt,
"R136, R138, R140, R141, R142, R25, R29, R316, R319, R323, R34, R386, R76",13,1k,R_0402_1005Metric,,,,smt,
"R14, R17, R20, R308",4,10,R_0402_1005Metric,,,,smt,
R145,1,DNP,R_0402_1005Metric,,,Yes,smt,
"R16, R195, R21, R221, R23, R285, R295, R299, R30, R366, R367, R370, R51, R58, R67, R72, R75, R79, R84, R88",20,0,R_0402_1005Metric,,,,smt,
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
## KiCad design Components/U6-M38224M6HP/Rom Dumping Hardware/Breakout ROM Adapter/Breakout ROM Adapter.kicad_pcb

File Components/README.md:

## PROM Dump

Here is a list of microcontrollers used on the PC110.
You can find the binary used on them with the disassembler approach.

|Designator|Part#  |Functions           |Notes                             |
|----------|-------|--------------------|----------------------------------|
|U6        |M38223*|Power Control, Front LCD & More|[Notes](U6-M38224M6HP/)|
|U67       |M38813*|Keyboard Controller|[Notes](U67-M38813E4HP/)           |

## Die level investigation

This part is a collaboration with [John McMaster](https://siliconpr0n.org/archive/doku.php?id=ibm:pc110)

|Designator|Part#      |Functions           |Images | Notes                             |
|----------|-----------|--------------------|-------|-----------------------------------|
|U75       |D17137AGT  |Trackpoint          |[Images](https://siliconpr0n.org/archive/doku.php?id=mcmaster:nec:d17137agt)|[Notes](U75-D17137AGT/)|
|U35       |Pluto      |Gate Array          |[Images](https://siliconpr0n.org/archive/doku.php?id=mcmaster:rios:z10s10922-00)|[Notes](U35-Pluto/)|
|U21       |Bowman     |Gate Array          |[Images](https://siliconpr0n.org/archive/doku.php?id=mcmaster:rios:63g33f1017)|[Notes](U21-Bowman/)|
|U61       |VL82C420FC5|Chipset, RTC, DMA, Intrupt Controller, Timer             |[Images](https://siliconpr0n.org/archive/doku.php?id=mcmaster:rios:vl82c420fc5-c)|[Notes](U61-VL82C420FC5/)|

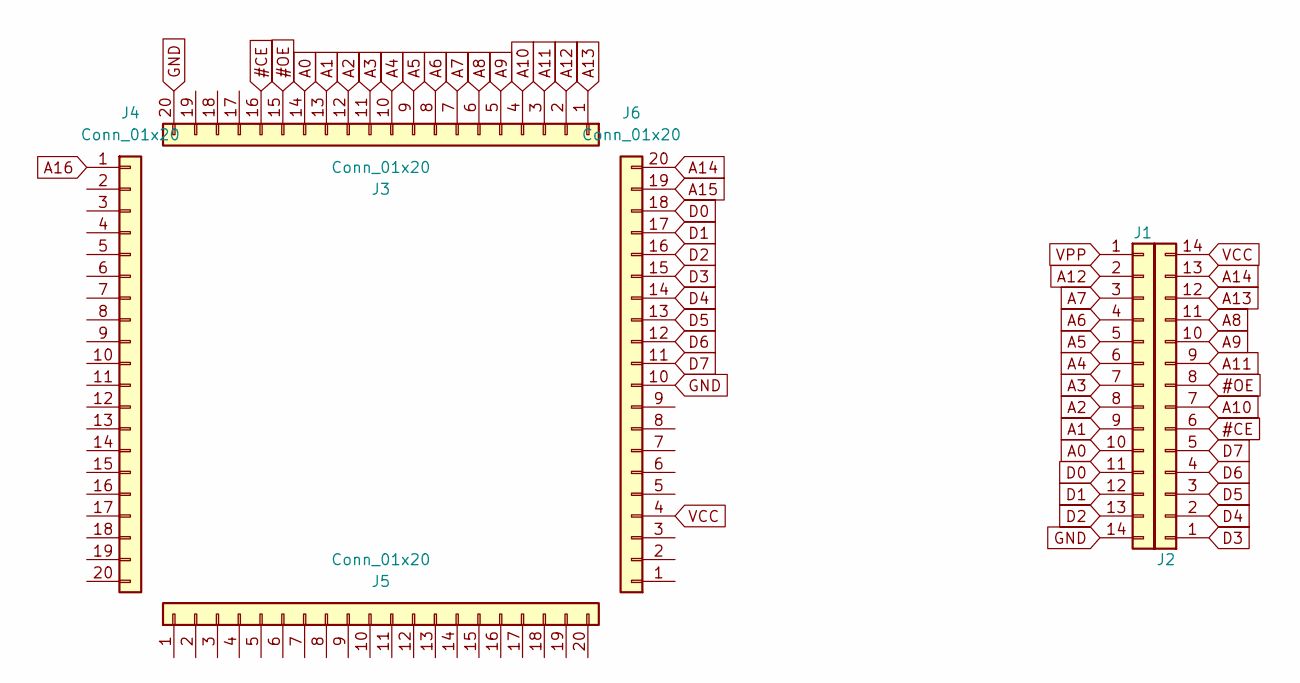
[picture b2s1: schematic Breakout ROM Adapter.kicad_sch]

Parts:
J1, J2: Conn_01x14; PinHeader_1x14_P2.54mm_Vertical
J3, J4, J5, J6: Conn_01x20; PinSocket_2x10_P2.54mm_Vertical

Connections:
#CE: J2.6, J3.16
#OE: J2.8, J3.15
A0: J1.10, J3.14
A1: J1.9, J3.13
A2: J1.8, J3.12
A3: J1.7, J3.11
A4: J1.6, J3.10
A5: J1.5, J3.9
A6: J1.4, J3.8
A7: J1.3, J3.7
A8: J2.11, J3.6
A9: J2.10, J3.5
A10: J2.7, J3.4
A11: J2.9, J3.3
A12: J1.2, J3.2
A13: J2.12, J3.1
A14: J2.13, J6.20
A15: J6.19
A16: J4.1
D0: J1.11, J6.18
D1: J1.12, J6.17
D2: J1.13, J6.16
D3: J2.1, J6.15
D4: J2.2, J6.14
D5: J2.3, J6.13
D6: J2.4, J6.12
D7: J2.5, J6.11
GND: J1.14, J3.20, J6.10
VCC: J2.14, J6.4
VPP: J1.1

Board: 2 copper layers, 6 parts (0 on the bottom side), 27 nets, no tracks yet.
